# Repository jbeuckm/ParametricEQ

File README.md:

# ParametricEQ
From http://www.all-electric.com/schematic/mix-eq.htm

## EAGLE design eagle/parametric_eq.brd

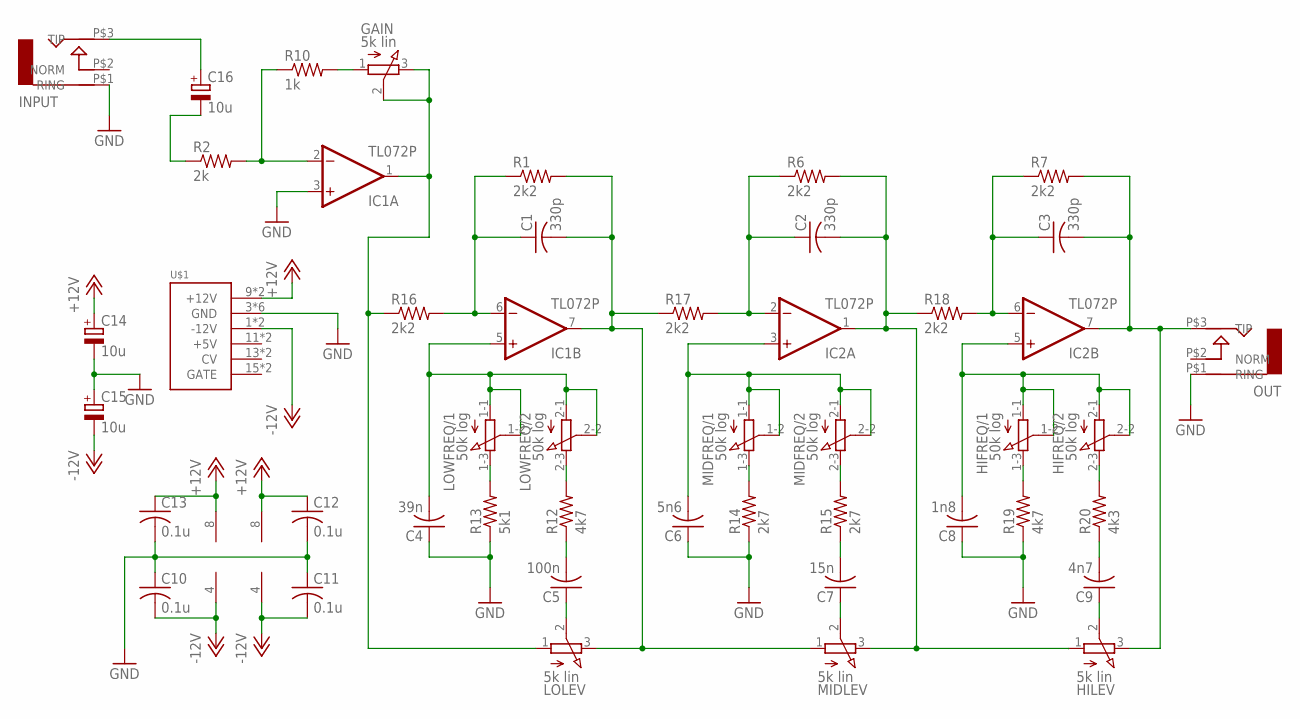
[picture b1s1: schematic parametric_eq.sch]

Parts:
C1, C2, C3: 330p; C050-050X075
C4: 39n; C050-050X075
C5: 100n; C050-050X075
C6: 5n6; C050-050X075
C7: 15n; C050-050X075
C8: 1n8; C050-050X075
C9: 4n7; C050-050X075
C10, C11, C12, C13: 0.1u; C025-030X050
C14, C15, C16: 10u; B45181A
GAIN: 5k lin; PTD901
HIFREQ: 50k log; PTD902
HILEV: 5k lin; PTD901
IC1, IC2: TL072P; DIL08
INPUT: AUDIO-JACK; ERTHENVAR-JACK-90DEG
LOLEV: 5k lin; PTD901
LOWFREQ: 50k log; PTD902
MIDFREQ: 50k log; PTD902
MIDLEV: 5k lin; PTD901
OUT: AUDIO-JACK; ERTHENVAR-JACK-90DEG
R1, R6, R7, R16, R17, R18: 2k2; 0207/10
R2: 2k; 0207/10
R10: 1k; 0207/10
R12, R19: 4k7; 0207/10
R13: 5k1; 0207/10
R14, R15: 2k7; 0207/10
R20: 4k3; 0207/10
U$1: POWER; POWER_16

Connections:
+12V: C12.1, C13.1, C14.+, IC1.8 (V+), IC2.8 (V+), U$1.9 (+12V), U$1.10 (+12V)
-12V: C10.2, C11.2, C15.-, IC1.4 (V-), IC2.4 (V-), U$1.1 (-12V), U$1.2 (-12V)
GND: C4.1, C6.1, C8.1, C10.1, C11.1, C12.2, C13.2, C14.-, C15.+, IC1.3 (+IN), INPUT.P$1 (RING), OUT.P$1 (RING), R13.1, R14.1, R19.1, U$1.3 (GND), U$1.4 (GND), U$1.5 (GND), U$1.6 (GND), U$1.7 (GND), U$1.8 (GND)
unnamed: IC1.2 (-IN), R2.2, R10.1
unnamed: GAIN.1 (A), R10.2
unnamed: C2.1, IC2.2 (-IN), R6.1, R17.2
unnamed: C3.1, IC2.6 (-IN), R7.1, R18.2
unnamed: C1.1, IC1.6 (-IN), R1.1, R16.2
unnamed: C1.2, IC1.7 (OUT), LOLEV.3 (E), MIDLEV.1 (A), R1.2, R17.1
unnamed: C2.2, HILEV.1 (A), IC2.1 (OUT), MIDLEV.3 (E), R6.2, R18.1
unnamed: C3.2, HILEV.3 (E), IC2.7 (OUT), OUT.P$3 (TIP), R7.2
unnamed: C16.+, INPUT.P$3 (TIP)
unnamed: LOWFREQ.1-3 (E), R13.2
unnamed: C5.2, R12.1
unnamed: LOWFREQ.2-3 (E), R12.2
unnamed: C5.1, LOLEV.2 (S)
unnamed: C7.1, MIDLEV.2 (S)
unnamed: C7.2, R15.1
unnamed: MIDFREQ.2-3 (E), R15.2
unnamed: MIDFREQ.1-3 (E), R14.2
unnamed: HIFREQ.1-3 (E), R19.2
unnamed: HIFREQ.2-3 (E), R20.2
unnamed: C9.2, R20.1
unnamed: C9.1, HILEV.2 (S)
unnamed: C4.2, IC1.5 (+IN), LOWFREQ.1-1 (A), LOWFREQ.1-2 (S), LOWFREQ.2-1 (A), LOWFREQ.2-2 (S)
unnamed: GAIN.2 (S), GAIN.3 (E), IC1.1 (OUT), LOLEV.1 (A), R16.1
unnamed: C16.-, R2.1
unnamed: C6.2, IC2.3 (+IN), MIDFREQ.1-1 (A), MIDFREQ.1-2 (S), MIDFREQ.2-1 (A), MIDFREQ.2-2 (S)
unnamed: C8.2, HIFREQ.1-1 (A), HIFREQ.1-2 (S), HIFREQ.2-1 (A), HIFREQ.2-2 (S), IC2.5 (+IN)

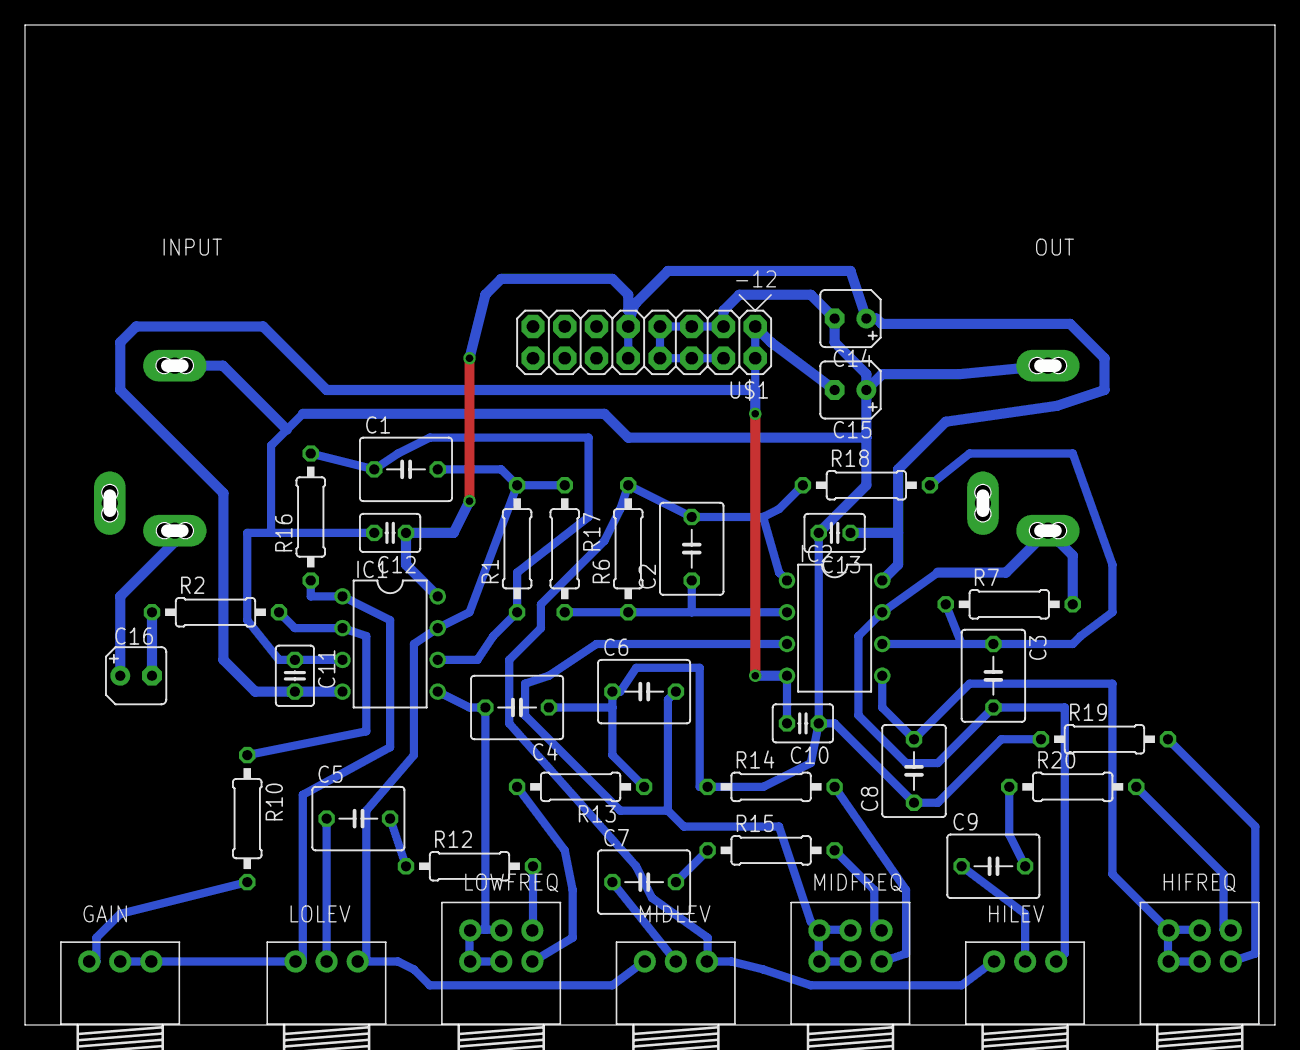
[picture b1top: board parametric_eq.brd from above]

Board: 2 copper layers, 100.0 x 80.0 mm, 42 parts (0 on the bottom side), 29 nets.

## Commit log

2015-11-12 initla commit
2015-11-12 added stolen image
2015-11-12 adding components
2015-11-13 some connections
2015-11-13 all components
2015-11-13 schematic screenshot
2015-11-13 bourns ptd pots
2015-11-13 parts are on the board
2015-11-13 autorouting
2015-11-13 almost routed
2015-11-13 routed
2015-11-13 power filter caps
2015-11-13 dc reject cap
2015-11-13 improved traces
2015-11-15 ferrite beads and thick traces
2015-11-15 first trial cut
2015-11-21 7mm 15n cap, new schematic png
2015-11-21 labeled panel
2015-11-21 panel cut and works
2016-01-05 working panel
